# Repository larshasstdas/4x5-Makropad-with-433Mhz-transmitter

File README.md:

# 4x5-Makropad-with-433Mhz-transmitter

This project is about a Makropad that has 20 keys in a 4x5 matrix with a 433Mhz transmitter that is used to power my PC. Every key has an indiviually LED that will be changeable with the daemon on the PC. Here is a short [Demo Video](https://www.youtube.com/shorts/1YbLsw79irE).

---

## Motivation

In a previous project i made a [wireless power switch for my PC](https://github.com/larshasstdas/Remote-PC-Power-Switch) but as it is only a singular button it feels quite chunky. And i also always had the interest in controlling my LED strips in my room and my PC lighting i got the idea of making a makropad that combines all those features. It should also have usual makropad funktion like adjusting the sound volume and shortcuts. 

---

## How it works

The RP2040 registers which key is pressed. It send that information to a daemon on my pc which has the information of what that key actually does. The programm can also send information to the makropad to what each LED should be. If the button is pressed that is used for turning the PC on the daemon can't answer because the PC is turned of. If the RP2040 does not get a signal back it sends the signal to the stx882 module resulting in turning the PC on. It can use a different function afterwards because the daemon can answer if that button is pressed.

---

## Features

- **remote PC wake** – a 433 MHz transmitter powers on the PC if the daemon is not responding (pc is turned off)
- **individual RBG per key** - different modes and each key can have an idividual color
- **Multiple layouts** - with the press of a button all keys can have a different function
- **Sleep mode** - if the PC is turned off the macropad enters a sleep mode

---

## PCB

I am using the RP2040 as a microcontroller it has everything i need and can be soldered onto the pcb with castelladed pads. The same goes for the 433MHz transmitter module the STX882. I also have the option to add a display but I am leaving that open as of now. Furthermore there are Hotswap pockets so i can easily swap broken switches. And for the LED I am using the SK6812MINI-E, a reverse mount LED. The switches are using a matrix so they need less pins and the LEDs are in an addressable LED chain.

All the PCB files are in the KiCad Folder.

---

## Bill of Materials

Bought the parts so they would be as cheap as possible. Did not buy the display pins as i do not plan on using it for now. It is just an option for the future.

| Part                      | Description                                       | Qty | Unit Price | Link |
| ------------------------- | ------------------------------------------------- | --- | ---------- | ---- |
| Waveshare RP2040-Zero     | MCU module, USB-C, castellated                    | 1   | 4.00€      | [Eckstein](https://eckstein-shop.de/WaveShare-RP2040-Zero-MCU-Board-Mini-Version) |
| STX882                    | 433 MHz ASK/OOK transmitter (+ spring antenna)    | 1   | 6.99€      | [Amazon](https://www.amazon.de/dp/B0D3TGHD7H/) |
| SK6812MINI-E              | Addressable RGB LED, reverse mount                | 20  | 6.59€      | [Amazon](https://www.amazon.de/gp/product/B0DQ8HXSQS/) |
| 74AHCT1G125               | Level shifter 3.3V→5V for LED data line (SOT-353) | 1   | 0.20€      | [Reichelt](https://www.reichelt.de/de/de/shop/produkt/tristate-buffer_enable_2_5_5_v_sot-353-5-219156) |
| Gateron Pro Milky Yellow  | Linear 5-pin hotswap switch                       | 20  | 6.80€      | [inputgear](https://inputgear.de/products/gateron-pro-milky-yellow-switch?variant=56226523775320) |
| Kailh MX Hotswap Socket   | MX hotswap socket (THT)                           | 20  | 7.83€      | [Amazon](https://www.amazon.de/gp/product/B07K8CCMQZ/) |
| Keycaps 1u                | Opaque keycaps (light shows around base)          | 20  | 10.71€     | [Amazon](https://www.amazon.de/gp/product/B0F1YQGJ35/) |
| 1N4148W                   | Matrix diode, 100V 150mA (SOD-123)                | 20  | 0.40€      | [Reichelt](https://www.reichelt.de/de/de/shop/produkt/kleinsignal-schalt-diode_100_v_150_ma_sod-123-219382) |
| 100nF capacitor           | Decoupling, X7R 50V (0603)                        | 21  | 0.63€      | [Reichelt](https://www.reichelt.de/de/de/shop/produkt/mlcc_0603_100nf_50v_x7r_-5_-429035) |
| 330 Ω resistor            | LED data-line series resistor (0603)              | 1   | 0.02€      | [Reichelt](https://www.reichelt.de/de/de/shop/produkt/smd-widerstand_0603_330_ohm_100_mw_1_-89424) |
| I2C display header        | 4-pin Dupont, optional display (2.54mm)           | 1   | -          | – |
| PCB                       | pcb ordered on jlcpcb                             | 1   | 33.67€     | – |
| 3D-printed case           | Top + bottom, filament                            | 1   | ~1.00€     | – |
| **Total**                 |                                                   |     | **78.84€** | |

---

## Case

The CAD files for the case are in the CAD folder. There are the source files from creo parametric (my cad tool), the step-files and the stl-files each in one folder. They contain a file for the top and the bottom part and the Creo folder also has the assembly file for the makropad which you can see below. The only files needed for 3D.printing are the case_bottom and cas_top files. The rest are only used for the assembly.

---

## How it is build

The pcb is soldered on a hot plate and some parts by soldering iron. The switches get placed into the hotswaps and once that is done it is placed in the bottom half of the case. Afterwards the top part gets fitted onto the bottom part and the keycaps get pressed onto the switches.

---

## How to flash

I used VS Code with PlatformIO to flash the RP2040. Just connect with an USB-C cable and press the flash button bottom left.

---

## How to set up the daemon

1. Create and activating the venv. For that first use "cd C:\path\...\Makropad\Daemon", then "python -m venv venv" and last "venv\Scripts\Activate.ps1".
2. Install all the libarys. The versions are in the requirements.txt
3. Select the right COM port in the config.json
4. Press "Win + R" and type "shell:startup" so the startup folder opens.
5. Rightclick and add a new shortcut. Enter the location "C:\path\...\Makropad\Daemon\venv\Scripts\pythonw.exe main.py" for the shortcut. When you press enter you can choose a name.
6. Rightclick the new shortcut and go to properties. In "Start in" enter the daemon folder "C:\path\...\Makropad\Daemon" it must not include "\venv\Scripts".
7. Apply the changes.

---

## How to change or make a new layout

To change or make a new layout open the **config.json**. Under **"layouts"** you will find all the layouts and key definitions with what each key does. Each layout has their own name. The best way to start a new layout is to copy a existing layout an edit the keys. 

Each key need two types of information. First is the type of action and the other is a value for what action will be taken. In the following are the all types with what actions can be made:

|type           | value                                             | description                                                   |
|---------------|---------------------------------------------------|---------------------------------------------------------------|
|text           | can be a letter,number,character or word          | Types the value                                               |                            
|hotkey         | a key combination, e.g. Copy is `"ctrl" + "c"`    | Presses the key combo                                         |               
|media          | `volumeup`, `volumedown`                          | Media/volume control                                          |
|               | `next`, `prev`                                    | next song or video                                            |
|               | `playpause`                                       | pauses or continues playing something                         |
|               | `volumemute`, `micmute`, `bothmute`               | mutes audio                                                   |                                  
|led            | `nextMode`, `lastMode`                            | sets led mode                                                 |
|               | `brighten`, `darken`                              | adjusts led brightness                                        |
|               | `faster`, `slower`                                | adjusts mode speed (not every mode)                           |
|               | `nextColor`, `lastColor`                          | changes led color (not every mode)                            |
|               | `nextColorFine`, `lastColorFine`                  | changes the led color in smaller steps                        |                   
|overlay        | name of a layout, e.g `default` or `led`          | switches to that layout                                       |
|inactive       | number between `0`-`255`                          | no function, the value sets led brightness (0 = off)          |

Currently set layouts are default, led, led_2 and media. The mode for the LEDs continues as a layout is swapped, although some LEDs might turn off as the key could be set as inactiv with a value of 0. In the following picture is a visualization of the current layouts for handling the LEDs and media.

---

## Files

```
CAD/               Creo source files (top, bottom, pcb and assembly), stl files (top & bottom), step files
Deamon/            Python files for the daemon, requirements.txt with all the libary versions  
KiCad/             KiCad files, Gerber files (also as .zip), libarys, Pick&Place
RP2040_Code/       PlatformIO project with all files needed for flashing the RP2040
BOM.csv
```
---

## Hackatime

https://hackatime.hackclub.com/@larshasstdas/project/Makropad

## Planned Features

- an UI so the layout and LEDs can be set by drag & drop (this needs a whole rewriting of the code so the daemon can handle api)
- with the UI there could be layouts to handle smarthome functions e.g. led stripes
- a mode that reacts to music and an actual usage of the directly setting the leds mode
- a soundboard layout that plays safed sounds
- a display that shows what the buttons of the active layout do

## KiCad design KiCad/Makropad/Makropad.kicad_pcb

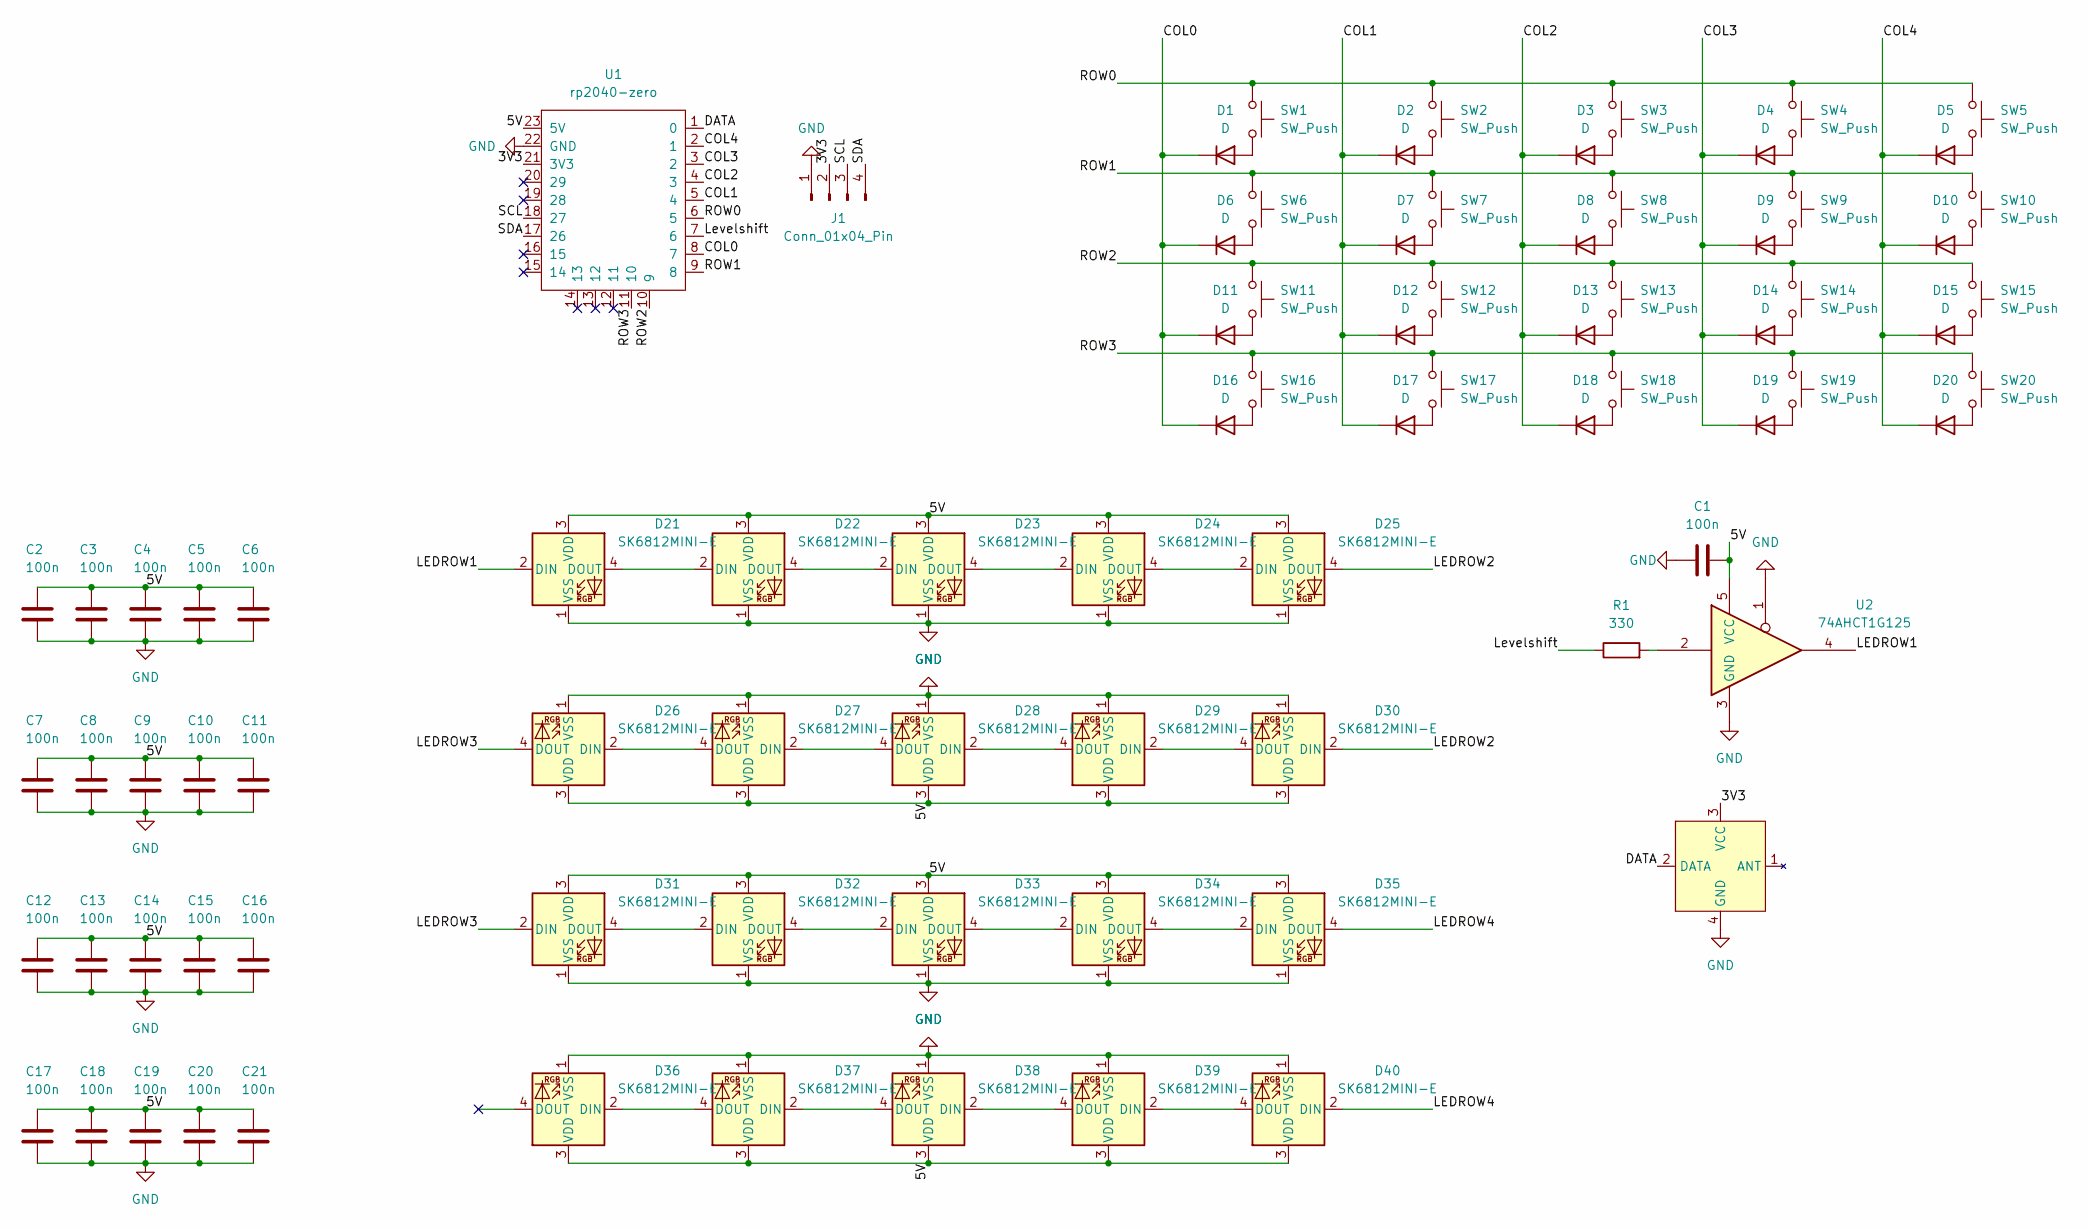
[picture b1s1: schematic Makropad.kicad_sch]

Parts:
C1, C2, C3, C4, C5, C6, C7, C8, C9, C10, C11, C12, C13, C14, C15, C16, C17, C18, C19, C20, C21: 100n; C_0603_1608Metric
D1, D2, D3, D4, D5, D6, D7, D8, D9, D10, D11, D12, D13, D14, D15, D16, D17, D18, D19, D20: D; D_SOD-123
D21, D22, D23, D24, D25, D26, D27, D28, D29, D30, D31, D32, D33, D34, D35, D36, D37, D38, D39, D40: SK6812MINI-E; LED_SK6812MINI-E_3.2x2.8mm_P1.5mm_ReverseMount
J1: Conn_01x04_Pin; PinHeader_1x04_P2.54mm_Horizontal
R1: 330; R_0603_1608Metric
SW1, SW2, SW3, SW4, SW5, SW6, SW7, SW8, SW9, SW10, SW11, SW12, SW13, SW14, SW15, SW16, SW17, SW18, SW19, SW20: SW_Push; SW_Hotswap_Kailh_MX_1.00u
U1: rp2040-zero; rp2040-zero-smd
U2: 74AHCT1G125; SOT-353_SC-70-5
U3: STX882

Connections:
/3V3: J1.2, U1.21 (3V3), U3.3 (VCC)
/5V: C1.2, C2.1, C3.1, C4.1, C5.1, C6.1, C7.1, C8.1, C9.1, C10.1, C11.1, C12.1, C13.1, C14.1, C15.1, C16.1, C17.1, C18.1, C19.1, C20.1, C21.1, D21.3 (VDD), D22.3 (VDD), D23.3 (VDD), D24.3 (VDD), D25.3 (VDD), D26.3 (VDD), D27.3 (VDD), D28.3 (VDD), D29.3 (VDD), D30.3 (VDD), D31.3 (VDD), D32.3 (VDD), D33.3 (VDD), D34.3 (VDD), D35.3 (VDD), D36.3 (VDD), D37.3 (VDD), D38.3 (VDD), D39.3 (VDD), D40.3 (VDD), U1.23 (5V), U2.5 (VCC)
/COL0: D1.1 (K), D6.1 (K), D11.1 (K), D16.1 (K), U1.8 (7)
/COL1: D2.1 (K), D7.1 (K), D12.1 (K), D17.1 (K), U1.5 (4)
/COL2: D3.1 (K), D8.1 (K), D13.1 (K), D18.1 (K), U1.4 (3)
/COL3: D4.1 (K), D9.1 (K), D14.1 (K), D19.1 (K), U1.3 (2)
/COL4: D5.1 (K), D10.1 (K), D15.1 (K), D20.1 (K), U1.2 (1)
/DATA: U1.1 (0), U3.2 (DATA)
/LEDROW1: D21.2 (DIN), U2.4
/LEDROW2: D25.4 (DOUT), D30.2 (DIN)
/LEDROW3: D26.4 (DOUT), D31.2 (DIN)
/LEDROW4: D35.4 (DOUT), D40.2 (DIN)
/Levelshift: R1.1, U1.7 (6)
/ROW0: SW1.1, SW2.1, SW3.1, SW4.1, SW5.1, U1.6 (5)
/ROW1: SW6.1, SW7.1, SW8.1, SW9.1, SW10.1, U1.9 (8)
/ROW2: SW11.1, SW12.1, SW13.1, SW14.1, SW15.1, U1.10 (9)
/ROW3: SW16.1, SW17.1, SW18.1, SW19.1, SW20.1, U1.11 (10)
/SCL: J1.3, U1.18 (27)
/SDA: J1.4, U1.17 (26)
GND: C1.1, C2.2, C3.2, C4.2, C5.2, C6.2, C7.2, C8.2, C9.2, C10.2, C11.2, C12.2, C13.2, C14.2, C15.2, C16.2, C17.2, C18.2, C19.2, C20.2, C21.2, D21.1 (VSS), D22.1 (VSS), D23.1 (VSS), D24.1 (VSS), D25.1 (VSS), D26.1 (VSS), D27.1 (VSS), D28.1 (VSS), D29.1 (VSS), D30.1 (VSS), D31.1 (VSS), D32.1 (VSS), D33.1 (VSS), D34.1 (VSS), D35.1 (VSS), D36.1 (VSS), D37.1 (VSS), D38.1 (VSS), D39.1 (VSS), D40.1 (VSS), J1.1, U1.22 (GND), U2.1, U2.3 (GND), U3.4 (GND)
unnamed: D1.2 (A), SW1.2
unnamed: D2.2 (A), SW2.2
unnamed: D3.2 (A), SW3.2
unnamed: D4.2 (A), SW4.2
unnamed: D5.2 (A), SW5.2
unnamed: D6.2 (A), SW6.2
unnamed: D7.2 (A), SW7.2
unnamed: D8.2 (A), SW8.2
unnamed: D9.2 (A), SW9.2
unnamed: D10.2 (A), SW10.2
unnamed: D11.2 (A), SW11.2
unnamed: D12.2 (A), SW12.2
unnamed: D13.2 (A), SW13.2
unnamed: D14.2 (A), SW14.2
unnamed: D15.2 (A), SW15.2
unnamed: D16.2 (A), SW16.2
unnamed: D17.2 (A), SW17.2
unnamed: D18.2 (A), SW18.2
unnamed: D19.2 (A), SW19.2
unnamed: D20.2 (A), SW20.2
unnamed: D21.4 (DOUT), D22.2 (DIN)
unnamed: D22.4 (DOUT), D23.2 (DIN)
unnamed: D23.4 (DOUT), D24.2 (DIN)
unnamed: D24.4 (DOUT), D25.2 (DIN)
unnamed: D26.2 (DIN), D27.4 (DOUT)
unnamed: D27.2 (DIN), D28.4 (DOUT)
unnamed: D28.2 (DIN), D29.4 (DOUT)
unnamed: D29.2 (DIN), D30.4 (DOUT)
unnamed: D31.4 (DOUT), D32.2 (DIN)
unnamed: D32.4 (DOUT), D33.2 (DIN)
unnamed: D33.4 (DOUT), D34.2 (DIN)
unnamed: D34.4 (DOUT), D35.2 (DIN)
unnamed: D36.2 (DIN), D37.4 (DOUT)
unnamed: D37.2 (DIN), D38.4 (DOUT)
unnamed: D38.2 (DIN), D39.4 (DOUT)
unnamed: D39.2 (DIN), D40.4 (DOUT)
unnamed: R1.2, U2.2

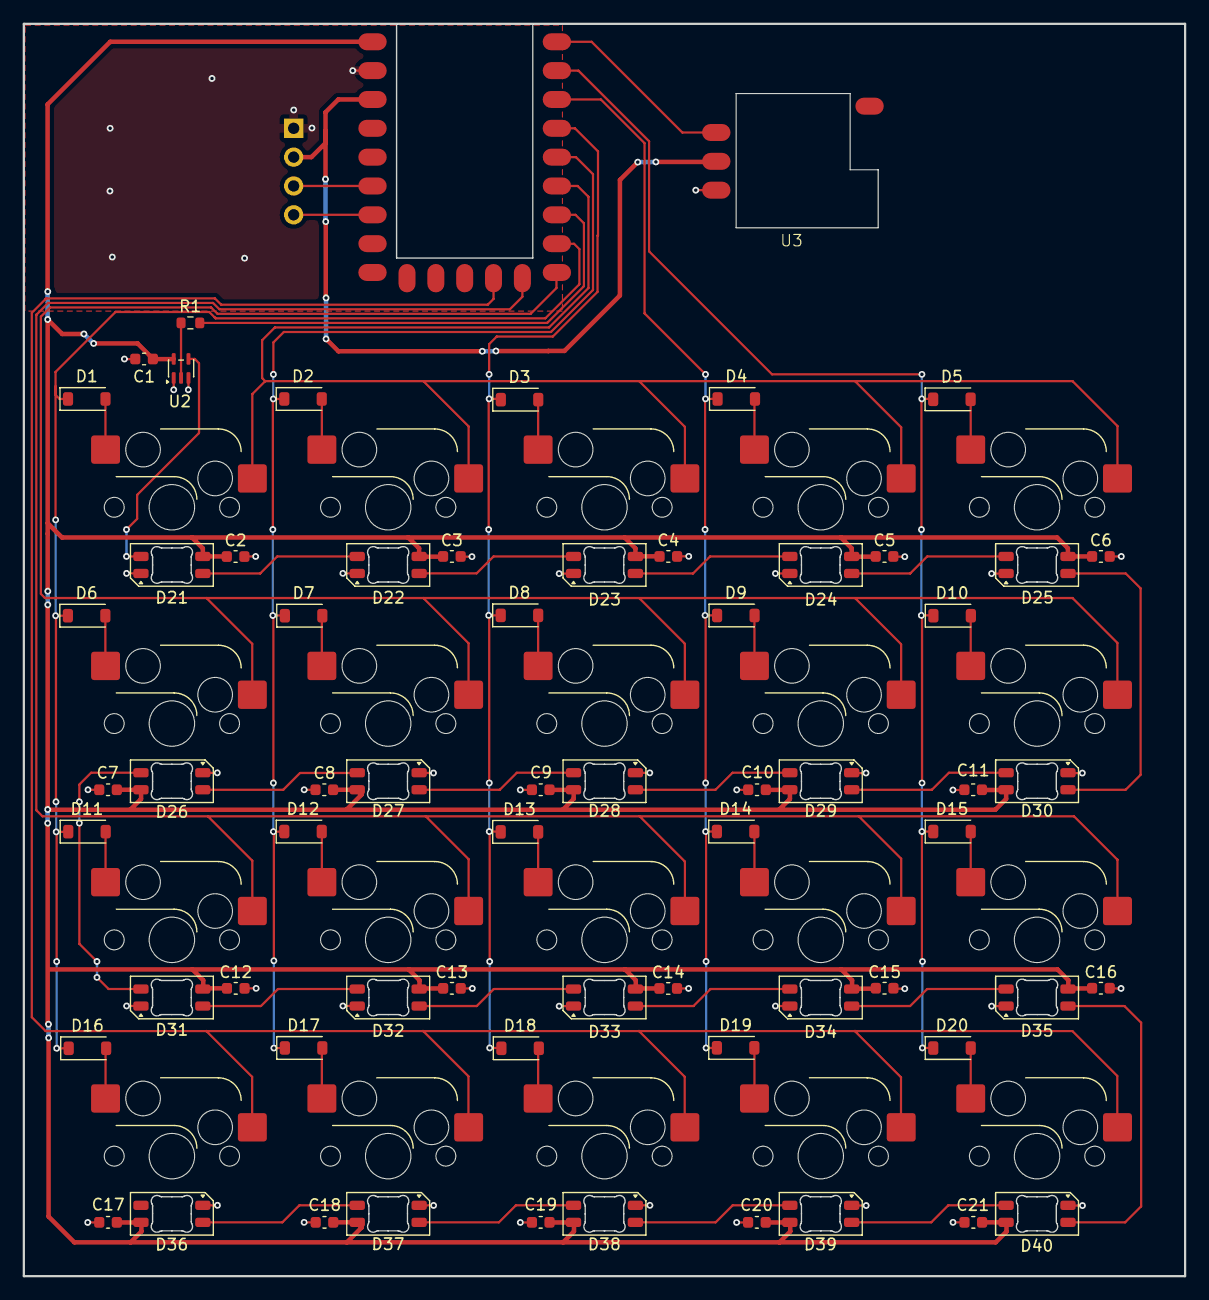
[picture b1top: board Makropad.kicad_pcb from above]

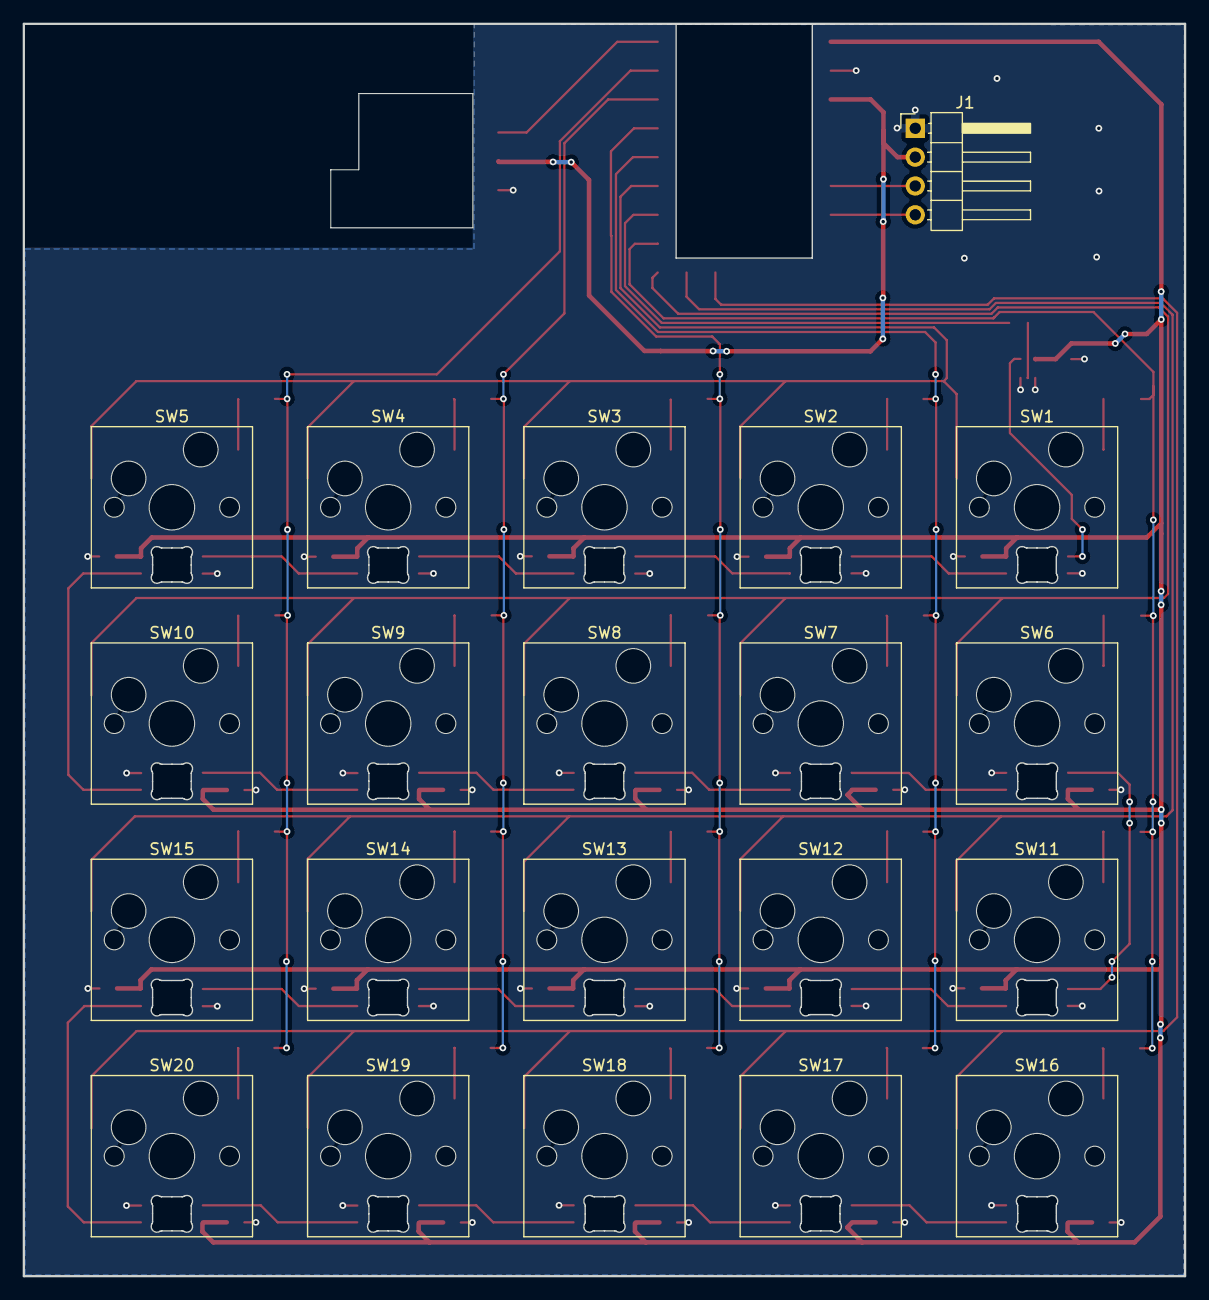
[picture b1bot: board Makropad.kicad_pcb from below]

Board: 2 copper layers, 102.3 x 110.3 mm, 86 parts (21 on the bottom side), 57 nets.
